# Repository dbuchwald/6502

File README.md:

# DB6502 - Dawid Buchwald's 6502 Computer

This repository contains all the work in progress during my build of Ben Eater's inspired 6502 8-bit computer similar to typical machines of the early 1980s. If you haven't seen Ben's videos, I would strongly suggest you start there:

[Ben Eater's 6502 project](https://eater.net/6502)

As stated above, this build is not 100% compatible with what Ben had done - and for a reason, described in next section.

If I had to explain shortly "what it is", the answer would be: simple, yet easy to expand, 8-bit CPU based computer designed and built with one goal only: to use it as a learning and tinkering platform to understand how computers really work. You can use it for simple things like understanding buses, clock cycles, instruction execution, but it also demonstrates more complex concepts like interrupts, interfaces to external components and device handling. More on that below. Everything, hopefully, is simple enough to wrap your head around by one person in couple of weeks.

## Why build something different

[Ben's videos](https://www.youtube.com/playlist?list=PLowKtXNTBypFbtuVMUVXNR0z1mu7dp7eH) on 6502 computer are absolutely awesome - it's one of the best sources in the whole Internet explaining how any computer works. The build he introduced is probably sufficient for most of the things you might ever want to build, and yet I decided to deviate from his design.

The rationale behind this project is pretty simple - the best way to test your understanding of certain subject is to try to expand on what you have learned. You never know if you understood something until you test it by introducing changes to original design - and I used this approach in this project to learn a lot. It was my first proper electronics project, so I would like to apologize for any mistakes. If you think something is off or could have been done differently - please go ahead and raise issue for the repo! All improvements are welcome!

## Why would you bother using DB6502 instead of BE6502

Basically, it gives you almost all the flexibility of Ben's buid without the hassle of breadboard connections for the critical components. You can still run all of Ben's programs (using second VIA port), but the days of looking for loose wire between RAM and CPU are over :) You can, obviously, still experiment with peripherals and breadboard connections using extension port and second VIA.

On top of that you get additional features like extra screen (via onboard connector), keyboard for more versatile input and finally all-in-one serial over USB terminal. You also get easy to use software ready to be installed on the machine to jumpstart your tinkering. When using bootloader you don't even have to flash the EEPROM more than once!

**Important note:** All of the content here is, and always will be open source and free to use, and I don't intend to make any profit out of it. The only way I get anything at all (and it's only small commission to be used for future PCBWay orders) is when you order my boards from PCBWay using the links posted below, but you are welcome to grab these gerber files and order the boards from another provider, or even from PCBWay, just by uploading gerbers to your account, if you don't want me to get the commission :)

## What is different

Compared to Ben's 6502 build I introduced the following changes:

1. Added [automatic power-up reset circuitry](Schematics/README.md#automatic-power-on-reset),
2. Changed [address decoder logic](Schematics/README.md#address-decoder-change) (**very important from compatibility perspective**),
3. Changed [LCD interface](Schematics/README.md#lcd-interface-change) from 8-bit to 4-bit (**very important from compatibility perspective**),
4. Added [additional VIA chip](Schematics/README.md#extra-via-chip) to provide easy expansion of the system,
5. Added [ACIA chip for serial communication](Schematics/README.md#extra-acia-chip-for-serial-communication),
6. Added (**optional - more on that later**) [USB-UART interface](Schematics/README.md#extra-usb-uart-interface-chip) for easy connectivity with PC,
7. Added [PS/2 keyboard port and ATtiny4313-based keyboard controller](Schematics/README.md#ps2-keyboard-interface-and-attiny4313-based-controller) to provide proper replacement for five pushbuttons in Ben's design,
8. Added [expansion port](Schematics/README.md#expansion-port) (not really deviation from Ben's build, save for one detail - unlike Ben's build, my version can support various interrupt sources, including the expansion port),
9. Modified [clock module](Schematics/README.md#modified-clock-module) (external),
10. Changed [compilator from VASM to CC65](Schematics/README.md#migration-from-vasm-to-cc65),
11. Added [simple way to choose clock source](Schematics/README.md#clock-input).

You might be wondering if this means that you can't run Ben's programs on DB6502 - and the answer is **YES YOU CAN**. Indeed, some changes to the code are necessary, but thanks to the additional VIA chip and with some changes to the addressing mode you can run any program from Ben's videos. If you want to use LCD in 8-bit mode, you can also use the additional VIA for it, ignoring the built-in LCD connector.

By the way, the opposite is also true - **you can compile and run my programs on Ben's computer**. There are special compilation flags that enable usage of Ben's address decoder. I will describe this in more detail in software section.

Detailed description and rationale for each change is discussed in [Schematics README](Schematics/README.md).

## Getting started

Okay, so it should be pretty clear what this project is about, so how to start playing with it? That really depends on what you decide to do:

- Stick with BE6502 and just use subset of provided software (either to install it in EEPROM, or just use it as reference for your own hacking),
- Build your own breadboard design based on this one with any modifications you can think of,
- Order PCBs of DB6502, solder the components and run provided software to see how it works and get started with your own designs.

To start from scratch it's actually easiest to select last option - after some waiting you will end up having pretty solid base to extend your design on.

### Using provided software with BE6502

If you decide to go down that route, head straight to the `Software` folder, where you will find several programs either identical or similar to what Ben has shown in his videos, but built with much more versatile toolchain.

If you want to read more, go ahead and read [Software folder](Software/README.md) section. Make sure to check out the [building software](Software/README.md#building-software) subsection, as it explains how to compile programs to run on BE6502 directly.

### Build your own breadboard design

Maybe you have already started expanding on Ben's build, or maybe you are just considering it now. If you want to check out how I did certain things, jump right into `Schematics` [folder](Schematics/README.md), where you will find KiCAD projects for all the components used in this project. Obviously the most important one is the `65C02_Computer` project, but there are some additional goodies there.

**Please note:** This part is not very well documented, I have assumed that anybody willing to dig into these schematics already knows how to read them.

Most of the decisions made during the schematic design were explained above. Justification for anything not covered here can be probably found in the [invaluable 6502 primer](http://wilsonminesco.com/6502primer/).

### Using my PCB design

This will be explained in the most detail, obviously. Start with getting [the PCBs](Schematics/README.md#ordering-pcb). **Please note:** clock module is entirely optional, but really useful for single stepping or slow clocking required by Ben Eater's design of Arduino Mega based bus analyzer. As explained in number of places here, you can either order PCBs from PCBWay directly or use your manufacturer of choice - it should have no impact on the final result.

## What's in the repo

Everything, basically. Schematics of the 6502 board, modified clock module, address decoder and other circuits I built during the project. Arduino sketches I used for debugging and simple programs used to test different features.

And, last but not least, full set of sample programs to follow Ben's videos on DB6502 plus my own bootloader/OS. The last two things are coming soon :)

### `Arduino` folder

There are several sketches there, and their full description is available is [separate README](Arduino/README.md).

### `AVR` folder

There are several projects there, used to experiment with pure `avr-gcc` development for Atmel AVR chips. While it has been interesting adventure that I plan to explore further in the future, it was easier to stick to standard Arduino tools for now and simply restructure code to work there.

### `Datasheets` folder

All the datasheets I used when designing DB6502, attached for reference.

### `Schematics` folder

All the KiCAD schematics for the 6502 computer, modified clock module and several others:

- 65C02_Computer - main schematic, including PCB design for DB6502 computer,
- Clock_module - schematic for the modified clock module, including PCB design,
- 555_troubleshoot - schematic of circuit used in [troubleshooting of clock module monostable noise issue](https://www.reddit.com/r/beneater/comments/edp1ls/noise_issue_in_monostable_mode_of_ben_eaters/),
- Address_decoder_basic - schematic of Ben Eater's address decoder for 6502 project,
- Address_decoder_basic_v2 - slightly modified version of the above,
- Address_decoder_extended - schematic of my own address decoder, used in the DB6502 computer.

There is dedicated [README](Schematics/README.md) in the folder, containing all the build-related details.

### `Software` folder

This one is the most important folder, as it contains range of different programs to play with the 6502 computer. Large subset of this programs can be built for Ben Eater's version of the 6502 computer without any changes. Some of them, however, use features available only in DB6502, like ACIA or keyboard connector. These can still be ran on Ben Eater's 6502 computer, assuming that compatible hardware is added to it.

The `Software` folder is currently divided into four main parts:

- `build` - temporary folder where all the build artifacts are created, including ROM binaries to be uploaded to EEPROM,
- `common` - common sources: include files with common constants, sources with shared function, configuration files for different address decoder logic modes, shared makefile used by all projects and small python script to optimize size of loadable modules,
- `rom` - set of projects used to create various ROM images to follow Ben's videos, test different features of the board and **some day** complete operating system for the computer,
- `load` - set of project containing loadable modules. These can be uploaded at runtime, without the need to flash the EEPROM. Basic bootloader is required, obviously, and the usage instructions are provided below.

There is also one "master" makefile located directly in the `Software` folder - it will build all the projects in `rom` and `load` subfolders.

There is dedicated [README](Software/README.md) in the folder, containing all the software-related details.

## Credits

This project would not be possible if not inspiration, support and help from many, many people:

- [Ben Eater](https://eater.net) - his videos inspired me to learn all this,
- [Dirk Grappendorf](https://grappendorf.net) - awesome documentation of his own 6502 project,
- [Wilson Mines Co.](http://wilsonminesco.com) - the best source of 6502-related information,
- [Dane Creek Photography](https://github.com/danecreekphotography) - for all his support and test driving the project,
- [u/transistorykris](https://www.reddit.com/user/transitorykris/) - his [KrisOS](https://github.com/transitorykris/krisos) is a great inspiration for my own OS development,
- [r/beneater community](https://www.reddit.com/r/beneater/) - for all the great ideas, feedback, creative spirit and exceptional support.

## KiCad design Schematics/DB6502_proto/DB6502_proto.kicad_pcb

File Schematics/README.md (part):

# 6502 system schematics

This documentation provides all the information regarding my variant of BE6502 computer:

- [Differences between the builds](#deviations-from-ben-eaters-design),
- [Instruction to order the PCBs](#ordering-pcb),
- [Getting started with the PCB](#building-pcb).

## Deviations from Ben Eater's design

This section describes details of each deviation from original BE6502 design.

### Automatic power-on reset

More of a cosmetic thing, but I liked the idea of computer running automatic reset on power-up. The added appeal was that the circuitry is actually copied from the original C64, which makes it instantly 1000x cooler :) You can read more on that here:
[Dirk Grappendorf's 6502 project - RESET](https://www.grappendorf.net/projects/6502-home-computer/reset-circuit.html)

As a side note - I would strongly recommend anybody interested to read about Dirk's project, he has plenty of great insight there!

### Address decoder change

This one was my first _real_ change as in it was _mine_. As Ben explained in his video, there are many ways to handle address decoding logic and he opted for model with 16K RAM, 16K I/O shadow and 32K ROM. He does note that it's a bit of a waste, but given the simplicity of the project it should not be a problem - and he is absolutely right.

That being said, I wanted more for my build. I knew I wanted to be able to load programs into my computer and I wanted to ensure that I provide user with as much RAM as possible. At the same time, I wanted to save some space on more optimized I/O shadow segment. And, most importantly, I wanted to test my understanding of how address decoding works. As stated above, the best way to learn is to change and test your hypothesis. If you want to learn more, I posted thread on [Reddit](https://www.reddit.com/r/beneater/comments/ej3lqi/65c02_address_decoder_for_32k_ram_24k_rom_and_2/) explaining what I did, how I did that and why I know it works. My build provides 32K RAM, 8K I/O shadow (for up to 11 devices), 24K ROM.

The key takeway here is that when porting Ben's programs you have to use this "mapping table":
|Segment|BE6502 |DB6502 |Comment |
|-------|-------------|-------------|------------------------------------------------------------------|
|RAM |0x0000-0x3fff|0x0000-0x7fff| |
|VIA1 | |0x9000 |Connected to keyboard/LCD/blink LED in my build |
|VIA2 |0x6000 |0x8800 |Can be used to run Ben's programs |
|ACIA | |0x8400 | |
|ROM |0x8000-0xffff|0xa000-0xffff|**First 8K are not accessible, but need to be burned to the chip**|

Simplest possible example - [Blink LED example](https://eater.net/downloads/makerom.py) from Ben's page:

```python
#
# Please see this video for details:
# https://www.youtube.com/watch?v=yl8vPW5hydQ
#
code = bytearray([
  0xa9, 0xff,         # lda #$ff
  0x8d, 0x02, 0x60,   # sta $6002

  0xa9, 0x55,         # lda #$55
  0x8d, 0x00, 0x60,   # sta $6000

  0xa9, 0xaa,         # lda #$aa
  0x8d, 0x00, 0x60,   # sta $6000

  0x4c, 0x05, 0x80,   # jmp $8005
  ])

rom = code + bytearray([0xea] * (32768 - len(code)))

rom[0x7ffc] = 0x00
rom[0x7ffd] = 0x80

with open("rom.bin", "wb") as out_file:
  out_file.write(rom)
```

The same program to run on my build:

```python
#
# Please see this video for details:
# https://www.youtube.com/watch?v=yl8vPW5hydQ
#
code = bytearray([
  0xa9, 0xff,         # lda #$ff
  0x8d, 0x02, 0x88,   # sta $8802 # MODIFIED HERE - use different VIA address

  0xa9, 0x55,         # lda #$55
  0x8d, 0x00, 0x88,   # sta $8800 # MODIFIED HERE - use different VIA address

  0xa9, 0xaa,         # lda #$aa
  0x8d, 0x00, 0x88,   # sta $8800 # MODIFIED HERE - use different VIA address

  0x4c, 0x05, 0xa0,   # jmp $a005 # MODIFIED HERE - different code start address, so different jump target
  ])

# MODIFIED BELOW - first 8KB of ROM are not really used, but need to be filled out; actual ROM starts at address
# 0xa000 and is of 24KB length
rom = bytearray([0xea] * 8192) + code + bytearray([0xea] * (24576 - len(code)))

rom[0x7ffc] = 0x00
rom[0x7ffd] = 0xa0 # MODIFIED HERE - different code start address

with open("rom.bin", "wb") as out_file:
  out_file.write(rom)
```

### LCD interface change

One of the silly things I decided to do, was to save pins on the first VIA chip and I decided on the following mapping:

| Port  | Pins    | Connection                                                                                |
| ----- | ------- | ----------------------------------------------------------------------------------------- |
| PORTA | CA1,CA2 | Keyboard controller read handshake - for IRQ based communication with keyboard controller |
| PORTA | D0-D7   | Keyboard controller data line - for transferring ASCII scancodes of pressed characters    |
| PORTB | CB1,CB2 | Not used, disconnected                                                                    |
| PORTB | D0      | Blink LED - to be used as the Arduino onboard LED, for easy debugging                     |
| PORTB | D1-D3   | LCD control signals (register select, R/W, enable)                                        |
| PORTB | D4-D7   | LCD data signals for 4-bit operation                                                      |

Afterwards it turned out that 4-bit operation is actually bit more complicated that 8-bit, and it breaks compatibility with Ben's programs. My best advice, if you want to run Ben's LCD programs on this build, is to use the second VIA port and 8-bit interface.

If you want to use onboard LCD conector and 4-bit interface it is suggested to use the code I supplied in this repo. It has all the data communication routines for LCD 4-bit operation tested and ready to go.

### Extra VIA chip

This one increases cost of the build, but in the end you have the whole chip to yourself, so you can hack whatever contraptions you can think of :)

This extra VIA chip can be also used to run Ben's programs, but you have to remember to update addressing mode.

### Extra ACIA chip for serial communication

This one is really important - thanks to ACIA chip you can actually forget about LCD and keyboard altogether, and all the input/output can be handled by the serial port. This also allows you to run programs that are loaded in runtime, over the serial line, making the ROM flashing no longer necessary. Obviously, there is a bootloader program required in ROM and one will be provided in this repo for your use shortly.

Currently my software supports only Rockwell R6551P chips and it uses fully asynchronous, buffered and IRQ driven send/receive operations. In future I plan to add support for WDC65C51 chips, but this requires change in source code to blocking send operation. Not a biggie, just not at the top of my priorities now. More on the ACIA chips below, in the PCB BOM section.

### Extra USB->UART interface chip

When I designed PCB for DB6502, I had one goal in mind: it must be possible to solder it with THT-only components. So, if you don't want to play with SMD soldering (which, admittably, is much easier that it seems), you can completely skip this component and connect serial over one of many UART->USB adapters. The same goes for the Micro-USB port - you can skip it, and use only USB-B port for power. Your call.

If you do decide to use FT230X chip onboard, you will have a 6502 computer that requires only USB cable - simply plug it in your PC, connect using serial terminal and you are good to go, nothing else needed. Power consumption is well below USB limits, even with LCD and external keyboard connected.

### PS/2 Keyboard interface and ATtiny4313 based controller

This was a bit of an overkill with the serial port addition, but I wanted DB6502 to be versatile and enable operation without PC connected.

Software to be uploaded to ATtiny is also provided in this repo and discussed in detail in dedicated section. You can either program the chip away from the board or use the included AVR ISP interface. I have successfully used USBASP programmer onboard, and since the reset lines between ATtiny and CPU/VIA/ACIA/FT230X are all connected, upload operation simply resets the whole computer without any risk for running programs. Pretty neat, that one :)

### Expansion port

The main purpose is to enable easy connection of Arduino-based debugger as used in Ben's videos. Everyone who managed to build the 6502 kit on breadboard knows how difficult it is to manage these connections and prevent them from unplugging system bus wires. In my build there is dedicated connector with several other options.

Beside address bus, data bus, clock and R/W signals, you will also find reset line (can be pulled low for external reset), IRQ input line (can be pulled low to signal interrupt, but can't be used to intercept system IRQs) and IOCS signal from address decoder indicating that CPU is now using address in I/O shadow range.

IOCS line can be used to add additional chips like ACIA or VIA via expansion port. VIA1 is selected using IOCS and A12 line (address 0b1001xxxxxxxxxxxx), VIA2 is selected using IOCS and A11 line (address 0b100x1xxxxxxxxxx), ACIA using IOCS and A10 line (address 0b100xx1xxxxxxxxxx), and you can access external I/O chips using addresses like IOCS and A9 for example (address 0b100xxx1xxxxxxxx). As you can see, it enables up to 8 external I/O chips (last two lines A0/A1 for register select) :)

### Modified clock module

I have also modified Ben's design of clock module used in both [8-bit breadboard computer](https://eater.net/8bit) and in [6502 computer](https://eater.net/6502). The reason here was pretty similar - modification introduced to validate own understanding of the original design. There was another thing, though - contents of my kit were not aligned with Ben's design (wrong kind of switch) and the design itself had serious flaw. Details of both of these things have been explained in detail [here](https://www.reddit.com/r/beneater/comments/eai6ke/issue_with_clock_kit_and_possible_solution_with/) and [here](https://www.reddit.com/r/beneater/comments/edp1ls/noise_issue_in_monostable_mode_of_ben_eaters/).

### Migration from VASM to CC65

As much as I liked VASM for small, simple projects, it became quite cumbersome to use when I wanted to introduce different addressing models. CC65 is basically much better compiler for anything 65(C)02 :)

If time allows, I will also provide special versions of Ben's programs written for VASM, but targeted for my own build.

### Clock input

Clock signal can be provided in one of three ways:

1. Use onboard 1MHz oscillator - simply put jumper on J1 connector two leftmost pins,
2. Use external clock module - remove the jumper from J1 connector, and connect clock signal to middle pin,
3. Use expansion port - remove jumper from J1 connector and provide clock signal via CLK pin of the expansion port.

Last option will be used in (planned currently) custom debugger board.

## Ordering PCB

[First revision of PCBs](https://github.com/dbuchwald/6502/releases/tag/pcb-v001) have been released (one for modified clock module and one for the computer itself). PCBs can be ordered here (**please note: I get small commission in coupons from PCBWay when ordering using these links**. If you don't want that to happen, please download gerbers from the GitHub rulease page and order directly via PCBWay home page):

[PCBWay Shared Projects - 65C02 Hobby Computer](https://www.pcbway.com/project/shareproject/65C02_Hobby_Computer.html)

[PCBWay Shared Projects - Clock Module](https://www.pcbway.com/project/shareproject/Modified_version_of_Clock_Module_by_Ben_Eater_s.html)

### 65C02 Computer Bill Of Materials

The following components are required for DB65C02 Computer

| Reference | Type                   | Value         | Description                        | Jameco                                                                  | DigiKey                                                                               |
| --------- | ---------------------- | ------------- | ---------------------------------- | ----------------------------------------------------------------------- | ------------------------------------------------------------------------------------- |
| C1        | Unpolarized Capacitor  | 100 nF        | Disk, 2.5mm raster                 | [151116](https://www.jameco.com/shop/ProductDisplay?productId=151116)   | [399-4151-ND](https://www.digikey.com/products/en?keywords=399-4151-ND)               |
| C2        | Unpolarized Capacitor  | 100 nF        | Disk, 2.5mm raster                 | [151116](https://www.jameco.com/shop/ProductDisplay?productId=151116)   | [399-4151-ND](https://www.digikey.com/products/en?keywords=399-4151-ND)               |
| C3        | Unpolarized Capacitor  | 100 nF        | Disk, 2.5mm raster                 | [151116](https://www.jameco.com/shop/ProductDisplay?productId=151116)   | [399-4151-ND](https://www.digikey.com/products/en?keywords=399-4151-ND)               |
| C4        | Unpolarized Capacitor  | 100 nF        | Disk, 2.5mm raster                 | [151116](https://www.jameco.com/shop/ProductDisplay?productId=151116)   | [399-4151-ND](https://www.digikey.com/products/en?keywords=399-4151-ND)               |
| C5        | Unpolarized Capacitor  | 100 nF        | Disk, 2.5mm raster                 | [151116](https://www.jameco.com/shop/ProductDisplay?productId=151116)   | [399-4151-ND](https://www.digikey.com/products/en?keywords=399-4151-ND)               |
| C6        | Polarized Capacitor    | 10 uF         | Tube, 2.5mm raster, 5mm diameter   | [330692](https://www.jameco.com/shop/ProductDisplay?productId=330692)   | [1189-2322-ND](https://www.digikey.com/products/en?keywords=1189-2322-ND)             |
| C7        | Unpolarized Capacitor  | 100 nF        | Disk, 2.5mm raster                 | [151116](https://www.jameco.com/shop/ProductDisplay?productId=151116)   | [399-4151-ND](https://www.digikey.com/products/en?keywords=399-4151-ND)               |
| C8        | Unpolarized Capacitor  | 10 nF         | Disk, 2.5mm raster                 |                                                                         | [399-4150-ND](https://www.digikey.com/products/en?keywords=399-4150-ND)               |
| C9        | Unpolarized Capacitor  | 47 pF         | Disk, 2.5mm raster                 | [2300831](https://www.jameco.com/shop/ProductDisplay?productId=2300831) | [399-9737-ND](https://www.digikey.com/products/en?keywords=399-9737-ND)               |
| C10       | Unpolarized Capacitor  | 47 pF         | Disk, 2.5mm raster                 | [2300831](https://www.jameco.com/shop/ProductDisplay?productId=2300831) | [399-9737-ND](https://www.digikey.com/products/en?keywords=399-9737-ND)               |
| C11       | Polarized Capacitor    | 1000 uF       | Tube, 5mm raster, 10mm diameter    | [330722](https://www.jameco.com/shop/ProductDisplay?productId=330722)   | [1189-1745-ND](https://www.digikey.com/products/en?keywords=1189-1745-ND)             |
| C12       | Unpolarized Capacitor  | 100 nF        | Disk, 2.5mm raster                 | [151116](https://www.jameco.com/shop/ProductDisplay?productId=151116)   | [399-4151-ND](https://www.digikey.com/products/en?keywords=399-4151-ND)               |
| C13       | Unpolarized Capacitor  | 100 nF        | Disk, 2.5mm raster                 | [151116](https://www.jameco.com/shop/ProductDisplay?productId=151116)   | [399-4151-ND](https://www.digikey.com/products/en?keywords=399-4151-ND)               |
| C14       | Unpolarized Capacitor  | 100 nF        | Disk, 2.5mm raster                 | [151116](https://www.jameco.com/shop/ProductDisplay?productId=151116)   | [399-4151-ND](https://www.digikey.com/products/en?keywords=399-4151-ND)               |
| C15       | Unpolarized Capacitor  | 100 nF        | Disk, 2.5mm raster                 | [151116](https://www.jameco.com/shop/ProductDisplay?productId=151116)   | [399-4151-ND](https://www.digikey.com/products/en?keywords=399-4151-ND)               |
| C16       | Unpolarized Capacitor  | 100 nF        | Disk, 2.5mm raster                 | [151116](https://www.jameco.com/shop/ProductDisplay?productId=151116)   | [399-4151-ND](https://www.digikey.com/products/en?keywords=399-4151-ND)               |
| C17       | Unpolarized Capacitor  | 100 nF        | Disk, 2.5mm raster                 | [151116](https://www.jameco.com/shop/ProductDisplay?productId=151116)   | [399-4151-ND](https://www.digikey.com/products/en?keywords=399-4151-ND)               |
| D1        | LED                    | Green         | 5mm diameter (PWR)                 | [2279199](https://www.jameco.com/shop/ProductDisplay?productId=2279199) | [754-1263-ND](https://www.digikey.com/products/en?keywords=754-1263-ND)               |
| D2        | LED                    | Red           | 5mm diameter (TX)                  | [333973](https://www.jameco.com/shop/ProductDisplay?productId=333973)   | [754-1264-ND](https://www.digikey.com/products/en?keywords=754-1264-ND)               |
| D3        | LED                    | Green         | 5mm diameter (RX)                  | [2279199](https://www.jameco.com/shop/ProductDisplay?productId=2279199) | [754-1263-ND](https://www.digikey.com/products/en?keywords=754-1263-ND)               |
| D4        | LED                    | Red           | 5mm diameter (BLINK)               | [333973](https://www.jameco.com/shop/ProductDisplay?productId=333973)   | [754-1264-ND](https://www.digikey.com/products/en?keywords=754-1264-ND)               |
| FB1       | Ferrite bead small     |               |                                    | [1844580](https://www.jameco.com/shop/ProductDisplay?productId=1844580) | [490-10997-ND](https://www.digikey.com/products/en?keywords=490-10997-ND)             |
| J1        | Pin header 3x1         |               | 2.54mm raster                      |                                                                         | [2057-PH1-03-UA-ND](https://www.digikey.com/products/en?keywords=2057-PH1-03-UA-ND)   |
| J2        | Female pin header 6x1  |               | 2.54mm raster                      |                                                                         | [S7004-ND](https://www.digikey.com/products/en?keywords=S7004-ND)                     |
| J3        | USB B Micro            |               | Molex 105017-0001                  |                                                                         | [WM1399CT-ND](https://www.digikey.com/products/en?keywords=WM1399CT-ND)               |
| J4        | USB B                  |               | Standard THT horizontal USB B port | [2096245](https://www.jameco.com/shop/ProductDisplay?productId=2096245) | [2057-USB-B-S-RA-ND](https://www.digikey.com/products/en?keywords=2057-USB-B-S-RA-ND) |
| J5        | Barrel Jack            |               | Standard power input 2.1/5.5       | [101178](https://www.jameco.com/shop/ProductDisplay?productId=101178)   |                                                                                       |
| J6        | Mini-Din-6             |               | Standard THT PS/2 Keyboard port    | [119475](https://www.jameco.com/shop/ProductDisplay?productId=119475)   | [CP-2260-ND](https://www.digikey.com/products/en?keywords=CP-2260-ND)                 |
| J7        | Female pin header 16x2 |               | 2.54mm raster                      |                                                                         | [S7119-ND](https://www.digikey.com/products/en?keywords=S7119-ND)                     |
| J8        | Pin header 3x2         |               | AVR ISP 2.54mm raster              |                                                                         | [609-3234-ND](https://www.digikey.com/products/en?keywords=609-3234-ND)               |
| J9        | Pin header 12x1        |               | 2.54mm raster                      |                                                                         | [2057-PH1-12-UA-ND](https://www.digikey.com/products/en?keywords=2057-PH1-12-UA-ND)   |
| J10       | Pin header 12x1        |               | 2.54mm raster                      |                                                                         | [2057-PH1-12-UA-ND](https://www.digikey.com/products/en?keywords=2057-PH1-12-UA-ND)   |
| J11       | Female pin header 16x1 |               | 2.54mm raster                      |                                                                         | [S7049-ND](https://www.digikey.com/products/en?keywords=S7049-ND)                     |
| R1        | Resistor               | 1M            | 1/4 watt                           | [691585](https://www.jameco.com/shop/ProductDisplay?productId=691585)   |                                                                                       |
| R2        | Resistor               | 47K           | 1/4 watt                           | [691260](https://www.jameco.com/shop/ProductDisplay?productId=691260)   |                                                                                       |
| R3        | Resistor               | 10K           | 1/4 watt                           | [691104](https://www.jameco.com/shop/ProductDisplay?productId=691104)   |                                                                                       |
| R4        | Resistor               | 27            | 1/4 watt                           | [690486](https://www.jameco.com/shop/ProductDisplay?productId=690486)   |                                                                                       |
| R5        | Resistor               | 27            | 1/4 watt                           | [690486](https://www.jameco.com/shop/ProductDisplay?productId=690486)   |                                                                                       |
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
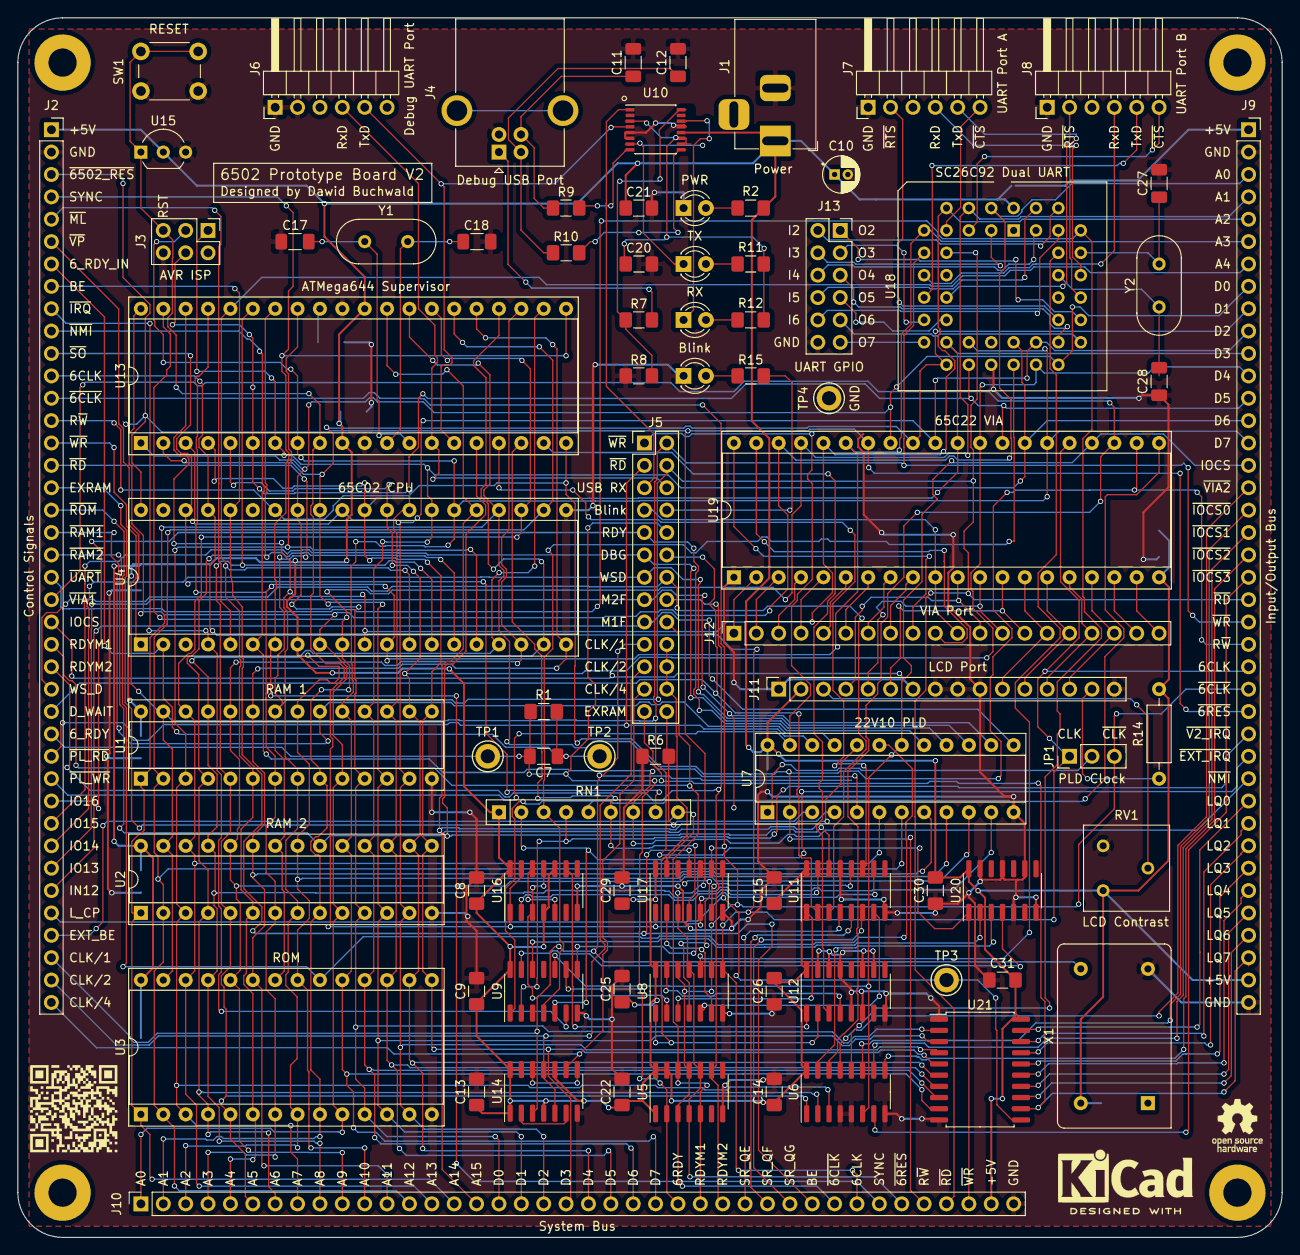
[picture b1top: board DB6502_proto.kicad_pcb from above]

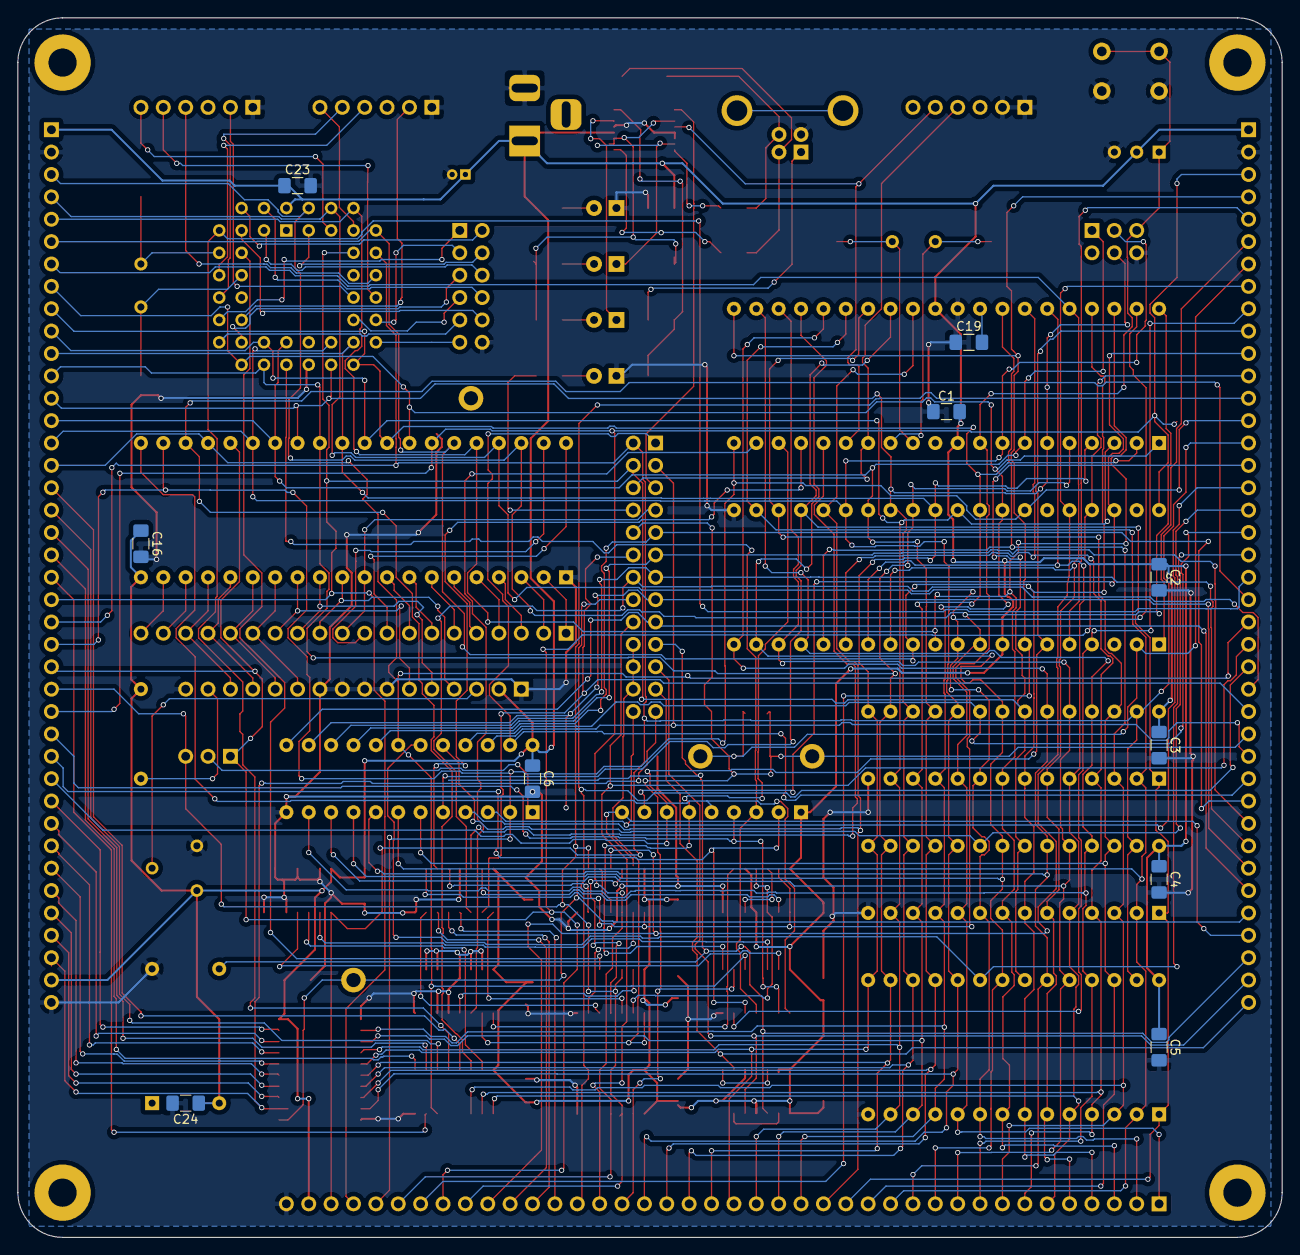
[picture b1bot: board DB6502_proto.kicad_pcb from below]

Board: 2 copper layers, 143.5 x 138.4 mm, 92 parts (10 on the bottom side), 171 nets.

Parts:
C1, C2, C3, C4, C5, C6, C8, C9, C13, C14, C15, C16, C19, C20, C21, C22, C23, C24, C25, C26, C29, C30, C31: 0,1uF; C_1206_3216Metric_Pad1.42x1.75mm_HandSolder
C7, C17, C18, C27, C28: 22pF; C_1206_3216Metric_Pad1.33x1.80mm_HandSolder
C10: 10uF; CP_Radial_D4.0mm_P1.50mm
C11, C12: 47pF; C_1206_3216Metric_Pad1.33x1.80mm_HandSolder
D1: PWR; LED_D3.0mm
D2: D_TX; LED_D3.0mm
D3: D_RX; LED_D3.0mm
D4: BLINK; LED_D3.0mm
J1: Power plug; BarrelJack_Horizontal
J2: Controls; PinSocket_1x40_P2.54mm_Vertical
J3: AVR ISP; PinHeader_2x03_P2.54mm_Vertical
J4: Debug USB; USB_B_OST_USB-B1HSxx_Horizontal
J5: JPR; PinHeader_2x13_P2.54mm_Vertical
J6: Debug UART; PinHeader_1x06_P2.54mm_Horizontal
J7: UART A; PinHeader_1x06_P2.54mm_Horizontal
J8: UART B; PinHeader_1x06_P2.54mm_Horizontal
J9: I/O Bus; PinSocket_1x40_P2.54mm_Vertical
J10: System Bus; PinSocket_1x40_P2.54mm_Vertical
J11: LCD Port; PinSocket_1x16_P2.54mm_Vertical
J12: VIA Ports; PinSocket_1x20_P2.54mm_Vertical
J13: UART GPIO; PinSocket_2x06_P2.54mm_Vertical
JP1: PLD CLK Selector; PinHeader_1x03_P2.54mm_Vertical
QR*****: https://tinyurl.com/ghdb6502; ghdb6502_03
R1, R2, R11, R12, R15: 470; R_1206_3216Metric_Pad1.42x1.75mm_HandSolder
R6, R7: 4K7; R_1206_3216Metric_Pad1.42x1.75mm_HandSolder
R8: 10K; R_1206_3216Metric_Pad1.42x1.75mm_HandSolder
R9, R10: 27; R_1206_3216Metric_Pad1.42x1.75mm_HandSolder
R14: 0R; R_Axial_DIN0207_L6.3mm_D2.5mm_P10.16mm_Horizontal
RN1: 4K7; R_Array_SIP9
RV1: 10K; Potentiometer_Bourns_3386F_Vertical
SW1: Reset; SW_PUSH_6mm_H4.3mm
TP1, TP2, TP4: TestPoint; TestPoint_Keystone_5005-5009_Compact
TP3: Latch_CP; TestPoint_Keystone_5005-5009_Compact
U1, U2: 71256; DIP-28_W7.62mm_Socket
U3: 28C256; DIP-28_W15.24mm_Socket
U4: 65C02S; DIP-40_W15.24mm_Socket
U5, U14, U16: 74AC74; SOIC-14_3.9x8.7mm_P1.27mm
U6: 74AC138; SOIC-16_3.9x9.9mm_P1.27mm
U7: 22V10C; DIP-24_W7.62mm_Socket
U8, U20: 74AC04; SOIC-14_3.9x8.7mm_P1.27mm
U9: 74HC21; SOIC-14_3.9x8.7mm_P1.27mm
U10: FT230XS; SSOP-16_4.4x5.2mm_P0.65mm
U11: 74HC595; SOIC-16_3.9x9.9mm_P1.27mm
U12: 74HC157; SOIC-16_3.9x9.9mm_P1.27mm
U13: ATmega644PA-PU; DIP-40_W15.24mm_Socket
U15: DS1813; TO-92_Inline_Wide
U17: 74AC08; SOIC-14_3.9x8.7mm_P1.27mm
U18: SC26C92; PLCC-44_THT-Socket
U19: 65C22S; DIP-40_W15.24mm_Socket
U21: 74AC574; SOIC-20W_7.5x12.8mm_P1.27mm
X1: 8MHz; Oscillator_DIP-14
Y1: 20MHz; Crystal_HC49-U_Vertical
Y2: 3,6864MHz; Crystal_HC49-U_Vertical

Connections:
6502_CLK: J2.12, J9.25, J10.33, JP1.1, U4.37, U8.8, U19.25
6502_CLK_IN: U8.13, U12.4
6502_RDY: C7.2, J2.28, J5.10, J10.25, R1.2, TP1.1, U5.2, U9.9
6502_RDY_IN: C7.1, J2.7, R1.1, TP2.1, U4.2
+5V: C1.1, C2.1, C3.1, C4.1, C5.1, C6.1, C8.1, C9.1, C10.1, C13.1, C14.1, C15.1, C16.1, C21.1, C22.1, C23.1, C24.1, C25.1, C26.2, C29.1, C30.2, C31.1, J1.1, J2.1, J9.1, J9.39, J10.39, J11.2, R2.1, R14.2, RN1.1, RV1.1, U1.28, U2.28, U3.28, U4.8, U5.1, U5.13, U5.14, U6.16, U7.24, U8.14, U9.14, U10.12, U11.16, U12.16, U13.10, U13.30, U14.1, U14.4, U14.10, U14.13, U14.14, U15.2, U16.4, U16.10, U16.14, U17.14, U18.44, U19.20, U20.14, U21.20, X1.14
/serial/ip2: J13.2, U18.40
/serial/ip3: J13.4, U18.3
/serial/ip4: J13.6, U18.43
/serial/ip5: J13.8, U18.42
/serial/ip6: J13.10, U18.41
/serial/op2: J13.1, U18.31
/serial/op3: J13.3, U18.15
/serial/op4: J13.5, U18.30
/serial/op5: J13.7, U18.16
/serial/op6: J13.9, U18.29
/serial/op7: J13.11, U18.17
/serial/v1pa0: J12.1, U19.2
/serial/v1pa1: J12.2, U19.3
/serial/v1pa2: J12.3, U19.4
/serial/v1pa3: J12.4, U19.5
/serial/v1pa4: J12.5, U19.6
/serial/v1pa5: J12.6, U19.7
/serial/v1pa6: J12.7, U19.8
/serial/v1pa7: J12.8, U19.9
/serial/v1pa8: J12.9, U19.40
/serial/v1pa9: J12.10, U19.39
/serial/v1pb1: J11.4, J12.12, U19.11
/serial/v1pb2: J11.5, J12.13, U19.12
/serial/v1pb3: J11.6, J12.14, U19.13
/serial/v1pb4: J11.11, J12.15, U19.14
/serial/v1pb5: J11.12, J12.16, U19.15
/serial/v1pb6: J11.13, J12.17, U19.16
/serial/v1pb7: J11.14, J12.18, U19.17
/serial/v1pb8: J12.19, U19.18
/serial/v1pb9: J12.20, U19.19
/supervisor/meta_sync: U16.5, U16.12
BE: J2.8, J10.31, U4.36, U17.11
BLINK_IN: J5.8, R15.2
BLINK_OUT: J5.7, J12.11, U19.10
CLK: J5.20, J5.22, J5.24, U8.1, U12.2
CLKSEL: U11.15, U16.2
CLK_1: J2.38, J5.19, U14.3, X1.8
CLK_2: J2.39, J5.21, U14.5, U14.11
CLK_4: J2.40, J5.23, U14.9
CLK_TOGGLE: U12.1, U16.9
DBG_CLK: U12.3, U13.19
DBG_RES: U8.5, U11.7
DBG_RxD: J5.6, J6.4, U13.14
DBG_TxD: J6.5, U10.4, U13.15
DBG_USBD+: R9.2, U10.8
DBG_USBD-: R10.2, U10.9
DBG_USB_RxD: J5.5, U10.1
DBG_WAIT: J2.27, J5.12, U11.2
EXRAM: J2.17, J5.26, R6.2, U7.3
EXT_BE: J2.37, RN1.9, U17.13
GND: C1.2, C2.2, C3.2, C4.2, C5.2, C6.2, C8.2, C9.2, C10.2, C11.2, C12.2, C13.2, C14.2, C15.2, C16.2, C17.1, C18.1, C19.1, C20.2, C21.2, C22.2, C23.2, C24.2, C25.2, C26.1, C27.2, C28.1, C29.2, C30.1, C31.2, D1.1, D4.1, J1.2, J2.2, J3.6, J4.4, J6.1, J6.2, J7.1, J8.1, J9.2, J9.40, J10.40, J11.1, J11.7, J11.8, J11.9, J11.10, J11.16, J13.12, R6.1, R8.1, RV1.3, SW1.2, TP4.1, U1.14, U2.14, U3.14, U4.21, U5.7, U6.4, U6.5, U6.8, U7.12, U8.7, U9.7, U10.5, U10.6, U10.13, U11.8, U11.13, U12.5, U12.6, U12.8, U12.10, U12.11, U12.13, U12.14, U12.15, U13.11, U13.31, U14.7, U15.3, U16.7, U17.7, U18.22, U19.1, U20.5, U20.7, U20.9, U20.11, U20.13, U21.1, U21.10, X1.7
IN12: J2.35, J5.17, U7.13
IO13: J2.34, J5.15, U7.14
IO14: J2.33, J5.13, U7.15
IO15: J2.32, J5.11, U7.16
IO16: J2.31, J5.9, U7.17
IOCS: J2.23, J9.16, U6.6, U7.18, U9.10, U19.24
LATCH_CP: J2.36, TP3.1, U17.8, U21.11
LATCH_Q0: J9.31, U21.19
LATCH_Q1: J9.32, U21.18
LATCH_Q2: J9.33, U21.17
LATCH_Q3: J9.34, U21.16
LATCH_Q4: J9.35, U21.15
LATCH_Q5: J9.36, U21.14
LATCH_Q6: J9.37, U21.13
LATCH_Q7: J5.25, J9.38, U21.12
unnamed: C11.1, J4.3, R9.1
unnamed: C12.1, J4.2, R10.1
unnamed: C17.2, U13.13, Y1.1
unnamed: C18.2, U13.12, Y1.2
unnamed: C19.2, U13.32
unnamed: C20.1, R11.1, R12.1, U10.3, U10.10, U10.11
unnamed: C27.1, U18.37, Y2.1
unnamed: C28.2, U18.36, Y2.2
unnamed: D1.2, R2.2
unnamed: D2.2, R11.2
unnamed: D3.2, R12.2
unnamed: D4.2, R15.1
unnamed: J4.1, R7.2
unnamed: J11.3, RV1.2
unnamed: J11.15, R14.1
unnamed: U14.2, U14.6
unnamed: U14.8, U14.12
unnamed: U9.8, U17.10
unnamed: U8.4, U17.12
unnamed: U9.12, U20.2
unnamed: U9.13, U20.4
PLD_CLK: JP1.2, U7.1
RAM1_~CS: J2.19, U1.20, U7.21
RAM2_~CS: J2.20, U2.20, U7.20
RDY_M1F: J2.24, J5.18, J10.26, U5.5, U5.12
RDY_M2F: J2.25, J5.16, J10.27, U5.9
ROM_~CS: J2.18, U3.20, U7.19
R~W: J2.14, J9.24, J10.36, U4.34, U7.2, U13.20, U19.22
SR_CLK: U11.11, U13.17
SR_DAT: U11.14, U13.16
SR_LATCH: U11.12, U17.6
SR_OUT: RN1.6, U13.18, U17.4
SR_QE: J10.28, U11.4
SR_QF: J10.29, U11.5
SR_QG: J10.30, U11.6
SYNC: J2.4, J10.34, U4.7, U13.21
UART_A_RxD: J7.4, U18.35
UART_A_TxD: J7.5, U18.33
UART_A_~CTS: J7.6, U18.8
UART_A_~RTS: J7.2, U18.32
UART_B_RxD: J8.4, U18.11
UART_B_TxD: J8.5, U18.13
UART_B_~CTS: J8.6, U18.5
UART_B_~RTS: J8.2, U18.14
UART_RES: U8.10, U18.38
VBUS_SENSE: R7.1, R8.2, U10.16
WS_DISABLE: J2.26, J5.14, U11.3
a0: J9.3, J10.1, U1.10, U2.10, U3.10, U4.9, U13.40, U18.2, U19.38
a1: J9.4, J10.2, U1.9, U2.9, U3.9, U4.10, U13.39, U18.4, U19.37
a2: J9.5, J10.3, U1.8, U2.8, U3.8, U4.11, U13.38, U18.6, U19.36
a3: J9.6, J10.4, U1.7, U2.7, U3.7, U4.12, U13.37, U18.7, U19.35
a4: J9.7, J10.5, U1.6, U2.6, U3.6, U4.13, U13.36
a5: J10.6, U1.5, U2.5, U3.5, U4.14, U6.1, U13.35
a6: J10.7, U1.4, U2.4, U3.4, U4.15, U6.2, U13.34
a7: J10.8, U1.3, U2.3, U3.3, U4.16, U6.3, U13.33
a8: J10.9, U1.25, U2.25, U3.25, U4.17, U7.11, U13.22
a9: J10.10, U1.24, U2.24, U3.24, U4.18, U7.10, U13.23
a10: J10.11, U1.21, U2.21, U3.21, U4.19, U7.9, U13.24
a11: J10.12, U1.23, U2.23, U3.23, U4.20, U7.8, U13.25
a12: J10.13, U1.2, U2.2, U3.2, U4.22, U7.7, U13.26
a13: J10.14, U1.26, U2.26, U3.26, U4.23, U7.6, U13.27
a14: J10.15, U1.1, U2.1, U3.1, U4.24, U7.5, U13.28
a15: J10.16, U4.25, U7.4, U13.29
d0: J9.8, J10.17, U1.11, U2.11, U3.11, U4.33, U13.1, U18.28, U19.33, U21.2
d1: J9.9, J10.18, U1.12, U2.12, U3.12, U4.32, U13.2, U18.18, U19.32, U21.3
d2: J9.10, J10.19, U1.13, U2.13, U3.13, U4.31, U13.3, U18.27, U19.31, U21.4
d3: J9.11, J10.20, U1.15, U2.15, U3.15, U4.30, U13.4, U18.19, U19.30, U21.5
d4: J9.12, J10.21, U1.16, U2.16, U3.16, U4.29, U13.5, U18.26, U19.29, U21.6
d5: J3.4, J9.13, J10.22, U1.17, U2.17, U3.17, U4.28, U13.6, U18.20, U19.28, U21.7
d6: J3.1, J9.14, J10.23, U1.18, U2.18, U3.18, U4.27, U13.7, U18.25, U19.27, U21.8
d7: J3.3, J9.15, J10.24, U1.19, U2.19, U3.19, U4.26, U13.8, U18.21, U19.26, U21.9
~6502_CLK: J2.13, J9.26, J10.32, JP1.3, U5.3, U5.11, U8.9, U8.12, U17.9
~6502_RES: J2.3, J9.27, J10.35, U4.40, U5.4, U5.10, U8.11, U17.3, U19.34
~CLK: U8.2, U16.3, U16.11
~DBG_BE: U8.3, U11.1
~DBG_RES: U8.6, U17.2
~DBG_RXLED: D3.1, U10.14
~DBG_TXLED: D2.1, U10.7
~EXT_IRQ: J9.29, RN1.2, U9.5
~IOCS0: J9.18, U6.11
~IOCS1: J9.19, U6.10
~IOCS2: J9.20, U6.9
~IOCS3: J9.21, U6.7
~IRQ: J2.9, U4.4, U9.6
~LATCH: U6.15, U20.3
~ML: J2.5, U4.5
~NMI: J2.10, J9.30, RN1.7, U4.6
~PLD_RD: J2.29, J5.3, U7.22
~PLD_WR: J2.30, J5.1, U7.23
~RD: J2.16, J5.4, J9.22, J10.37, U1.22, U2.22, U3.22, U18.10
~RES: J3.5, SW1.1, U11.10, U13.9, U15.1, U16.1, U16.13, U17.1, U17.5
~SO: J2.11, RN1.8, U4.38
~UART: J2.21, U6.12, U18.39
~UART_IRQ: RN1.3, U9.4, U18.24
~VIA1: J2.22, U6.14, U19.23
~VIA1_IRQ: RN1.5, U9.1, U19.21
~VIA2: J9.17, U6.13
~VIA2_IRQ: J9.28, RN1.4, U9.2
~VP: J2.6, U4.1
~WR: J2.15, J5.2, J9.23, J10.38, U1.27, U2.27, U3.27, U18.9, U20.1

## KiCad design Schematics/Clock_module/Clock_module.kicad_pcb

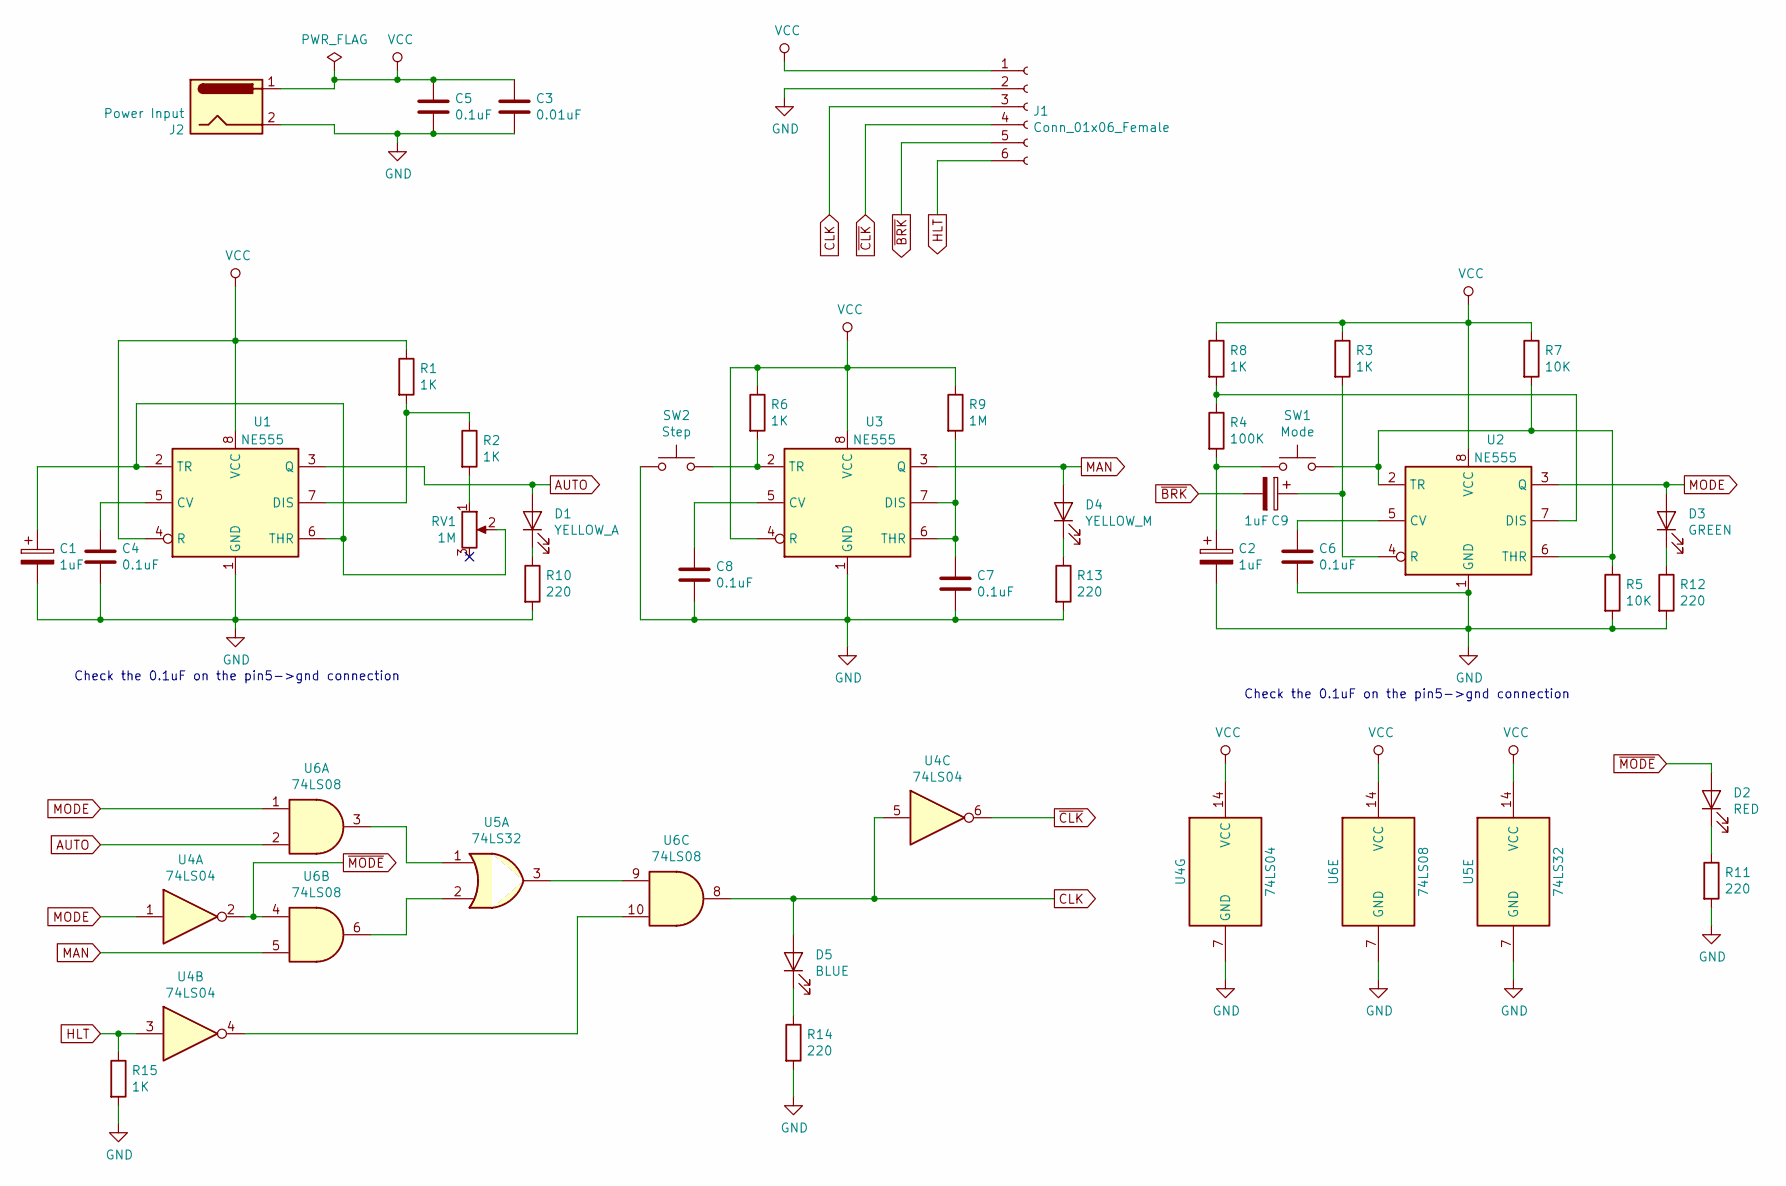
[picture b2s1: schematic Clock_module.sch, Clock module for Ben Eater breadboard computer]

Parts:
C1, C2, C9: 1uF; CP_Radial_D5.0mm_P2.50mm
C3: 0.01uF; C_Disc_D3.0mm_W2.0mm_P2.50mm
C4, C5, C6, C7, C8: 0.1uF; C_Disc_D3.0mm_W2.0mm_P2.50mm
D1: YELLOW_A; LED_D5.0mm
D2: RED; LED_D5.0mm
D3: GREEN; LED_D5.0mm
D4: YELLOW_M; LED_D5.0mm
D5: BLUE; LED_D5.0mm
J1: Conn_01x06_Female; PinSocket_1x06_P2.54mm_Vertical
J2: Power Input; BarrelJack_Horizontal
R1, R2, R3, R6, R8, R15: 1K; R_Axial_DIN0207_L6.3mm_D2.5mm_P7.62mm_Horizontal
R4: 100K; R_Axial_DIN0207_L6.3mm_D2.5mm_P7.62mm_Horizontal
R5, R7: 10K; R_Axial_DIN0207_L6.3mm_D2.5mm_P7.62mm_Horizontal
R9: 1M; R_Axial_DIN0207_L6.3mm_D2.5mm_P7.62mm_Horizontal
R10, R11, R12, R13, R14: 220; R_Axial_DIN0207_L6.3mm_D2.5mm_P7.62mm_Horizontal
RV1: 1M; Potentiometer_Piher_PT-10-V10_Vertical
SW1: Mode; SW_PUSH_6mm
SW2: Step; SW_PUSH_6mm
U1, U2, U3: NE555; DIP-8_W7.62mm_Socket
U4: 74LS04; DIP-14_W7.62mm_Socket
U5: 74LS32; DIP-14_W7.62mm_Socket
U6: 74LS08; DIP-14_W7.62mm_Socket

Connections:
AUTO: D1.2 (A), U1.3 (Q), U6.2
CLK: D5.2 (A), J1.3, U4.5, U6.8
GND: C1.2, C2.2, C3.2, C4.2, C5.2, C6.2, C7.2, C8.2, J1.2, J2.2, R5.2, R10.2, R11.2, R12.2, R13.2, R14.2, R15.2, SW2.1, U1.1 (GND), U2.1 (GND), U3.1 (GND), U4.7 (GND), U5.7 (GND), U6.7 (GND)
HLT: J1.6, R15.1, U4.3
MAN: D4.2 (A), U3.3 (Q), U6.5
MODE: D3.2 (A), U2.3 (Q), U4.1, U6.1
unnamed: C1.1, RV1.2, U1.2 (TR), U1.6 (THR)
unnamed: C2.1, R4.2, SW1.1
unnamed: C4.1, U1.5 (CV)
unnamed: C6.1, U2.5 (CV)
unnamed: C7.1, R9.2, U3.6 (THR), U3.7 (DIS)
unnamed: C8.1, U3.5 (CV)
unnamed: C9.1, R3.2, U2.4 (R)
unnamed: D1.1 (K), R10.1
unnamed: D2.1 (K), R11.1
unnamed: D3.1 (K), R12.1
unnamed: D4.1 (K), R13.1
unnamed: D5.1 (K), R14.1
unnamed: R1.2, R2.1, U1.7 (DIS)
unnamed: R2.2, RV1.1
unnamed: R4.1, R8.2, U2.7 (DIS)
unnamed: R5.1, R7.2, SW1.2, U2.2 (TR), U2.6 (THR)
unnamed: R6.2, SW2.2, U3.2 (TR)
unnamed: U4.4, U6.10
unnamed: U5.1, U6.3
unnamed: U5.2, U6.6
unnamed: U5.3, U6.9
VCC: C3.1, C5.1, J1.1, J2.1, R1.1, R3.1, R6.1, R7.1, R8.1, R9.1, U1.4 (R), U1.8 (VCC), U2.8 (VCC), U3.4 (R), U3.8 (VCC), U4.14 (VCC), U5.14 (VCC), U6.14 (VCC)
~BRK: C9.2, J1.5
~CLK: J1.4, U4.6
~MODE: D2.2 (A), U4.2, U6.4

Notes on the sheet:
Check the 0.1uF on the pin5->gnd connection

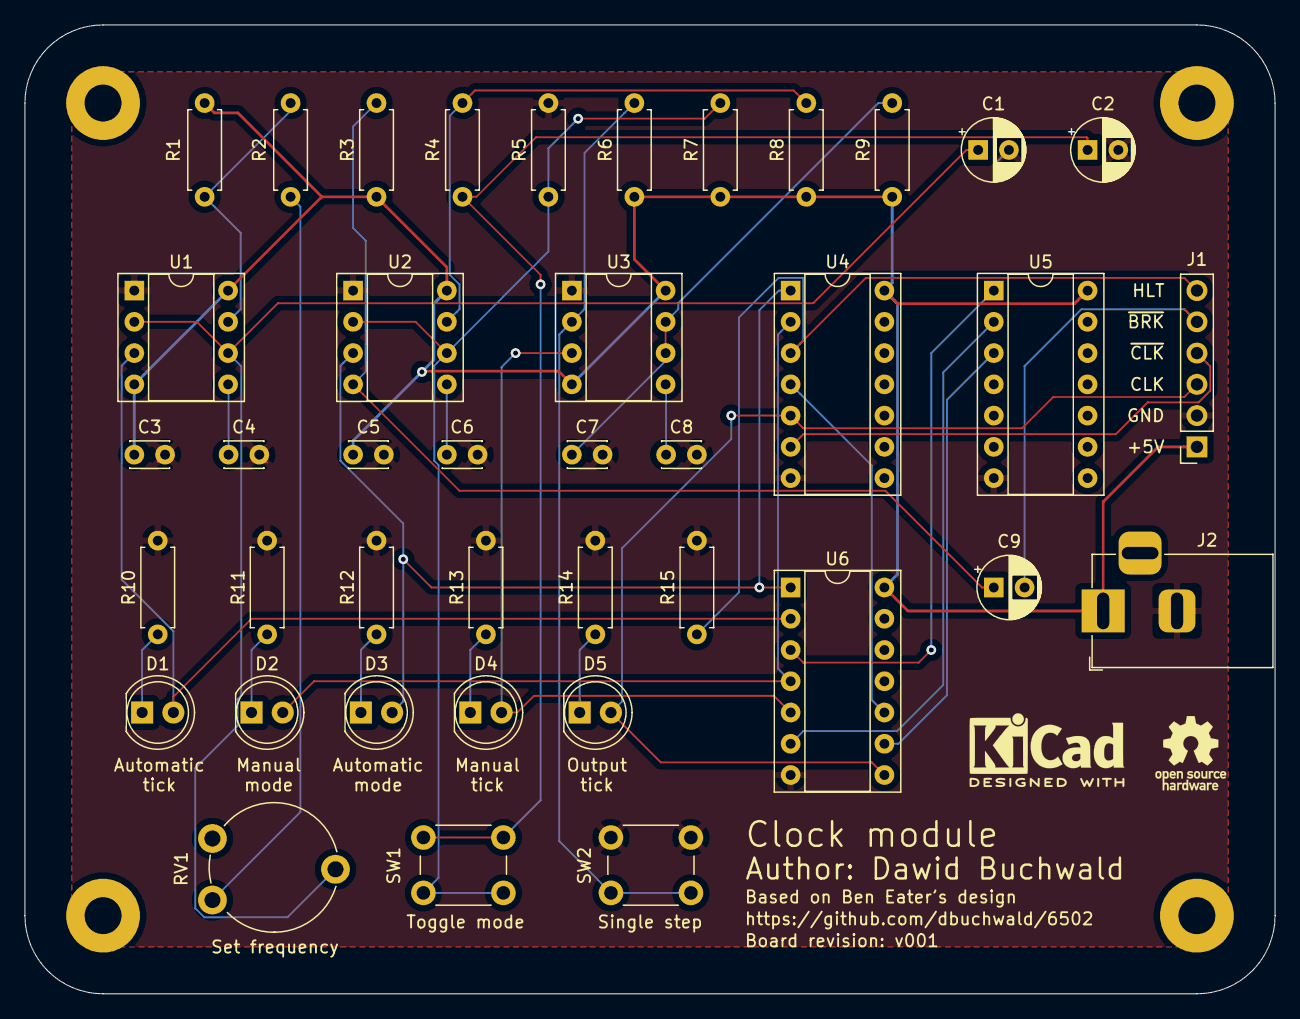
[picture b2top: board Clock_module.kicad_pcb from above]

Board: 2 copper layers, 101.6 x 78.7 mm, 40 parts (0 on the bottom side), 31 nets.
